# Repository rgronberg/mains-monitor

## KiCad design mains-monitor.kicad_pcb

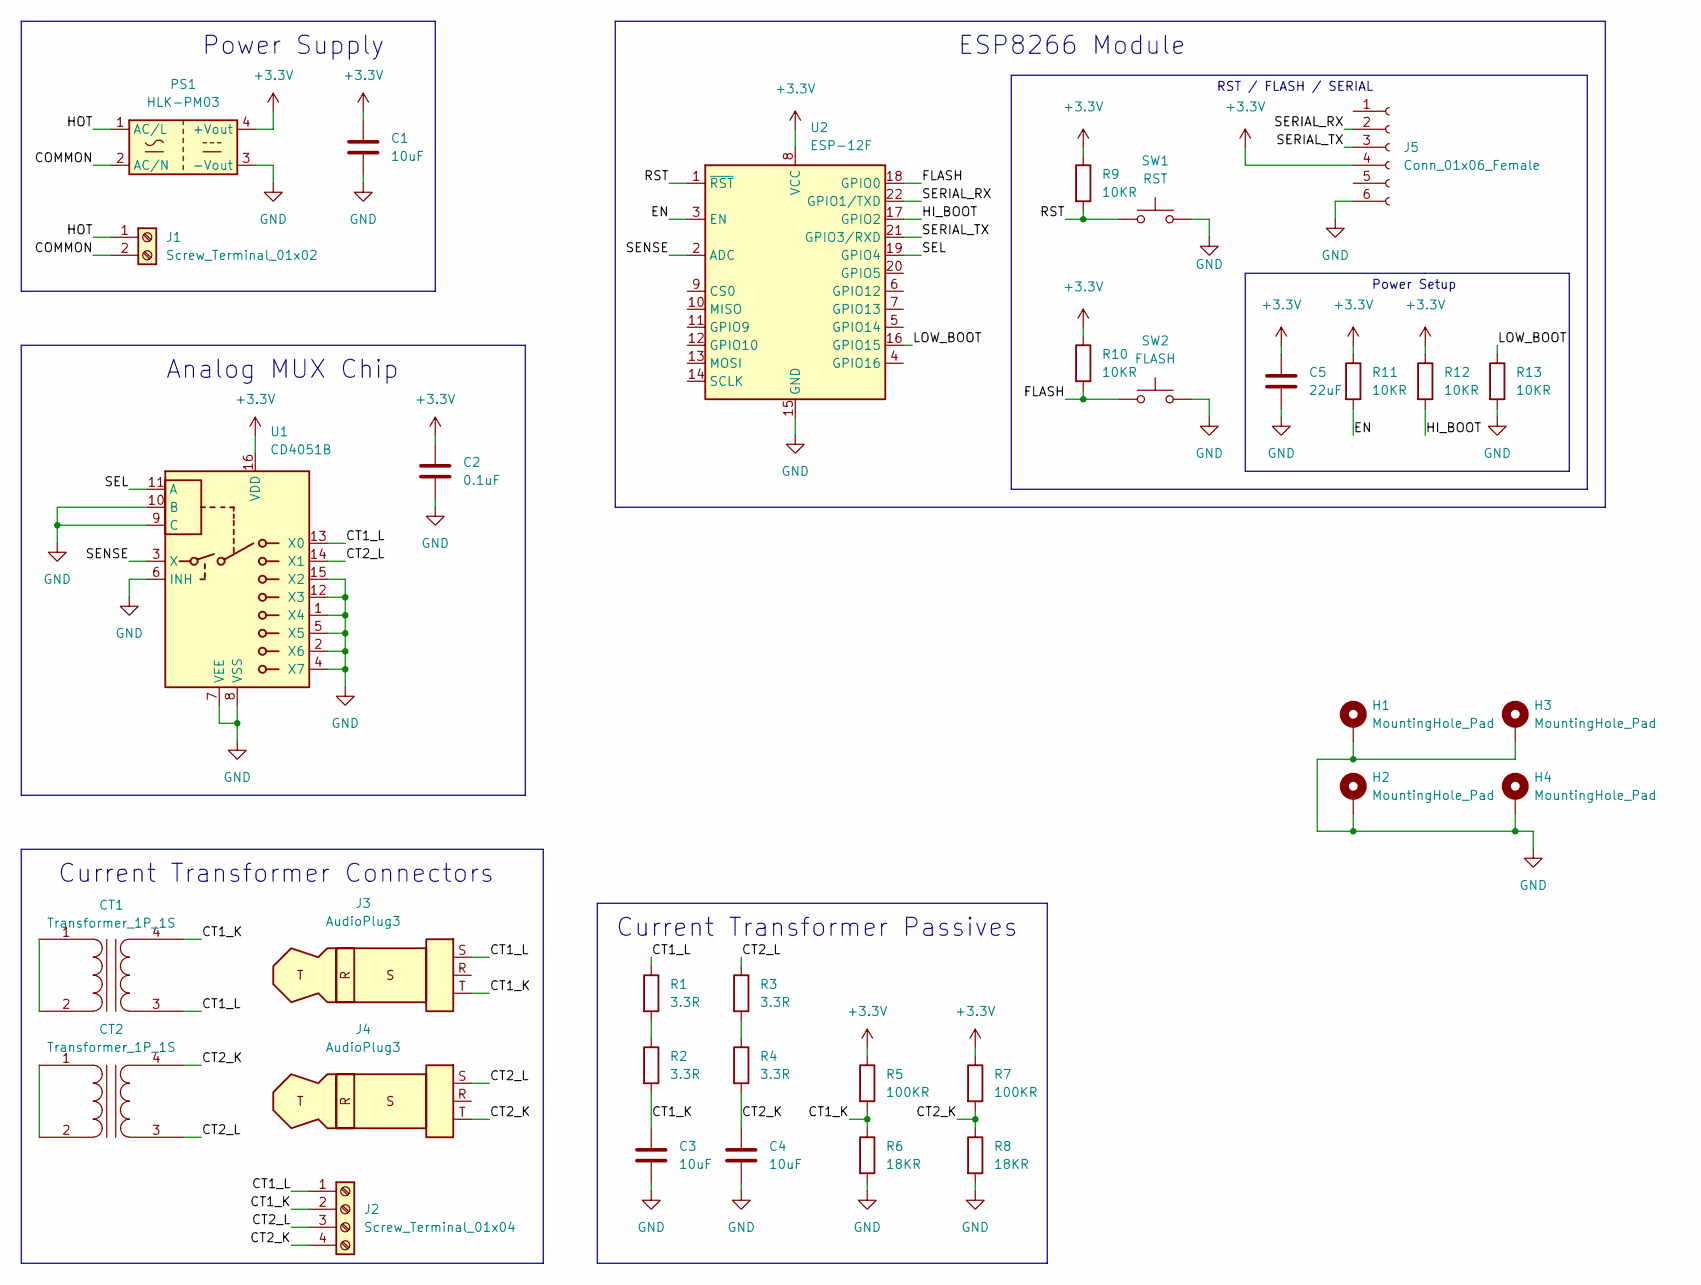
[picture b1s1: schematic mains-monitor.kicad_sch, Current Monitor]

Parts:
C1: 10uF; C_1206_3216Metric
C2: 0.1uF; C_1206_3216Metric
C3, C4: 10uF; C_0805_2012Metric
C5: 22uF; C_1206_3216Metric
CT1, CT2: Transformer_1P_1S
H1, H2, H3, H4: MountingHole_Pad; MountingHole_3.2mm_M3_Pad_Via
J1: Screw_Terminal_01x02; TerminalBlock_bornier-2_P5.08mm
J2: Screw_Terminal_01x04; TerminalBlock_Altech_AK300-4_P5.00mm
J3, J4: AudioPlug3; Jack_3.5mm_PJ320A_Horizontal
J5: Conn_01x06_Female; PinSocket_1x06_P2.54mm_Vertical
PS1: HLK-PM03; Converter_ACDC_HiLink_HLK-PMxx
R1, R2, R3, R4: 3.3R; R_0805_2012Metric
R5, R7: 100KR; R_0805_2012Metric
R6, R8: 18KR; R_0805_2012Metric
R9, R10, R11, R12, R13: 10KR; R_Axial_DIN0207_L6.3mm_D2.5mm_P7.62mm_Horizontal
SW1: RST; SW_PUSH_6mm
SW2: FLASH; SW_PUSH_6mm
U1: CD4051B; DIP-16_W7.62mm
U2: ESP-12F; ESP-12E

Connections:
+3.3V: C1.1, C2.1, C5.2, J5.4, PS1.4 (+Vout), R5.1, R7.1, R9.1, R10.1, R11.1, R12.1, U1.16 (VDD), U2.8 (VCC)
/COMMON: J1.2, PS1.2 (AC/N)
/CT1_K: C3.1, CT1.4 (SB), J2.2, J3.T, R2.2, R5.2, R6.1
/CT1_L: CT1.3 (SA), J2.1, J3.S, R1.1, U1.13 (X0)
/CT2_K: C4.1, CT2.4 (SB), J2.4, J4.T, R4.2, R7.2, R8.1
/CT2_L: CT2.3 (SA), J2.3, J4.S, R3.1, U1.14 (X1)
/EN: R11.2, U2.3 (EN)
/FLASH: R10.2, SW2.1, U2.18 (GPIO0)
/HI_BOOT: R12.2, U2.17 (GPIO2)
/HOT: J1.1, PS1.1 (AC/L)
/LOW_BOOT: R13.1, U2.16 (GPIO15)
/RST: R9.2, SW1.1, U2.1 (~RST)
/SEL: U1.11 (A), U2.19 (GPIO4)
/SENSE: U1.3 (X), U2.2 (ADC)
/SERIAL_RX: J5.2, U2.22 (GPIO1/TXD)
/SERIAL_TX: J5.3, U2.21 (GPIO3/RXD)
unnamed: CT1.1 (AA), CT1.2 (AB)
unnamed: CT2.1 (AA), CT2.2 (AB)
unnamed: R1.2, R2.1
unnamed: R3.2, R4.1

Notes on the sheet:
Power Supply
Current Transformer Connectors
Analog MUX Chip
Power Setup
RST / FLASH / SERIAL
Current Transformer Passives
ESP8266 Module

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
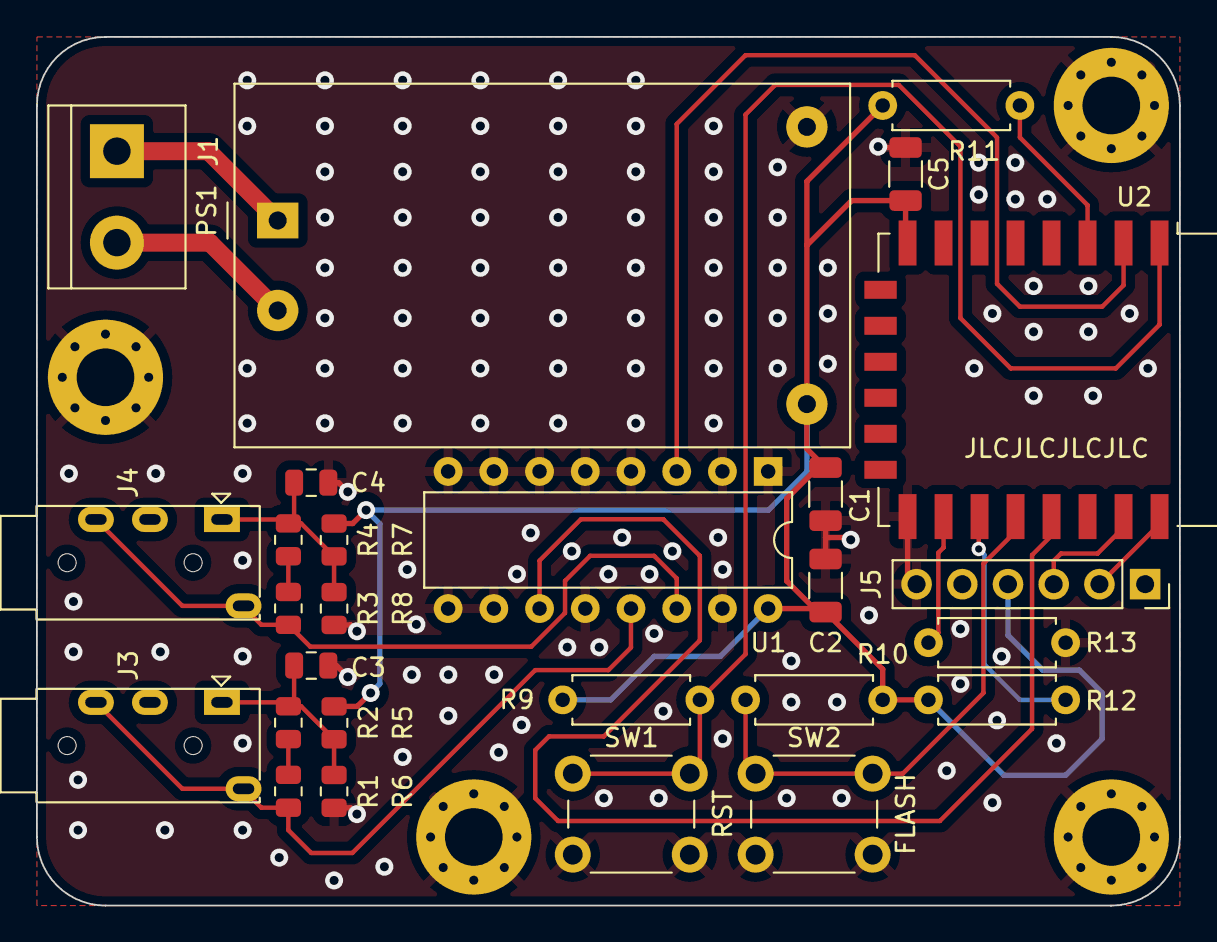
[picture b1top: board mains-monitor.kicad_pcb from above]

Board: 2 copper layers, 63.5 x 48.3 mm, 31 parts (0 on the bottom side), 19 nets.

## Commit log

2023-03-31 Initial commit: Reporting watts used to thingspeak
2023-03-31 Reporting daily/monthly kWh/watts
2023-03-31 Add EmonConfig class to store config in a file
2023-03-31 Update MainsMonitor to use config calibration and voltage
2023-03-31 Add ability to delete config file
2023-03-31 add .gigignore
2023-03-31 Reduce number of samples in MainsMonitor
2023-03-31 WIP: Only report to ThinkSpeak if we have meaningful values
2023-03-31 Add debug python server and basic web interface
2023-03-31 Refactor daily and monthly kWh into MainsMonitor class
2023-03-31 Add webserver and template population
2023-03-31 Add settings/config update to webserver
2023-03-31 Automatically save default config to disk
2023-03-31 Dont block while waiting for NTP time
2023-03-31 Use WifiManager
2023-03-31 Use api_key and channel from config
2023-03-31 Use flash button long hold to reset settings
2023-03-31 Reboot device if hostname is changed
2023-03-31 Change default current calibration
2023-03-31 Updated web form details
2023-03-31 Config ThingSpeak settings in wifi portal
2023-03-31 Convert mains-monitor from ino to cpp
2023-04-22 Change monthly reset date to the first
2024-11-23 Refactor repo structure
2024-11-23 Add PCB to repo
2025-04-23 KiCad changes
2025-04-23 Add configurable reset date

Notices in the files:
mains-monitor.kicad_sch:
Licence: WTFPL
